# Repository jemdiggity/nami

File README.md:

# Nami 波

An internal prototype for bolt-on equipment telemetry. A split-core current clamp senses the changing magnetic field around one insulated supply conductor without an electrical connection to it. The coin-cell-powered electronics sit in an enclosure outside the equipment. The intended application is 120/240 V AC, single-phase equipment up to 20 A; suitability for that installation remains to be validated.

Nami records one RMS current value each second, retains local history, and sends measurements over Thread to a powered local hub. BLE provides commissioning. The name means “wave”: we are picking up the waves from the wire and measuring them.

- [Product requirements and system diagrams](docs/PRD.md) — authoritative prototype specification.
- [Compact C0 hardware](hardware/nami-compact/README.md) — 24 × 32 mm, four-layer production layout candidate, renders and STEP model.
- [Rev A bench hardware](hardware/nami-rev-a/README.md) — KiCad schematics, routed PCB, BOM, verification and bring-up guide.
- [Earlier design explorations](docs/research/) — rationale and candidate circuits; superseded where they conflict with the PRD.

Status: bench and compact hardware design; feasibility validation remains. Native KiCad schematics and a routed prototype PCB are included; firmware and physical validation are not yet complete. Accuracy, battery life, packaging, and installation suitability remain unverified. The board is not a manufacturing or mains-installation release.

## Compact PCB

The compact C0 board is 24 × 32 mm with four copper layers. These snapshots show the current KiCad layout; the clamp, battery, and enclosure are external to the board.

### 3D model

**[Open the full-color interactive 3D model](https://jemdiggity.github.io/nami/viewer/)** — rotate, pan, zoom, or switch between front and back views. Click the preview below to open it.

[Download GLB with materials](docs/viewer/nami.glb) · [Download STEP for CAD](hardware/nami-compact/exports/nami-compact.step) · [Download STL](https://github.com/jemdiggity/nami/raw/refs/heads/main/hardware/nami-compact/exports/nami-compact.stl)

The interactive viewer uses GLB (glTF), preserving separate meshes and component colors with material finishes adjusted for browser lighting. STEP remains available for CAD, and STL for geometry-only viewing. Models use the available KiCad component bodies and are not a validated mechanical assembly.

### Front and back

| Front | Back |
| --- | --- |
|  |  |

[STEP model](hardware/nami-compact/exports/nami-compact.step) · [PCB layout](hardware/nami-compact/nami.kicad_pcb) · [Routing review](hardware/nami-compact/exports/routing-review.pdf)

## Schematics

The previews below are vector SVG exports from the compact KiCad project. Open an image to zoom in. The [complete schematic PDF](hardware/nami-compact/exports/nami-schematic.pdf) and [native KiCad schematic](hardware/nami-compact/nami.kicad_sch) are also available.

### Analog sensing

<details>
<summary>System overview</summary>

</details>

<details>
<summary>Power supply</summary>

</details>

<details>
<summary>Radio, processor, and storage</summary>

</details>

<details>
<summary>Clamp and wiring harness</summary>

</details>

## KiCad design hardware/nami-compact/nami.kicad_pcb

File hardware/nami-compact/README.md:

# Nami Compact C0 — production layout candidate

**24 × 32 mm, four copper layers, 1.0 mm nominal PCB thickness, components on both sides.** This reduces board area from the Rev A bench board's 7,125 mm² to 768 mm²: **89.22% smaller**. Open [nami.kicad_pro](nami.kicad_pro) in KiCad 10.

This is a routed, checked candidate for the product's electronics, not a qualified production release. The dimensions describe the PCB alone. Battery/holder, CT, burden assembly, wiring, strain relief and enclosure are separate. Accuracy, endurance and installed RF performance remain unmeasured.

| Review artifact | Contents |
|---|---|
| [Front render](exports/nami-top.png) / [back render](exports/nami-bottom.png) | Actual KiCad board geometry and library component models |
| [Size comparison](exports/size-comparison.svg) | Board outlines to scale |
| [Schematic PDF](exports/nami-schematic.pdf) | Five sheets, including the off-board CT burden |
| [STEP model](exports/nami-compact.step) | Board and available library models for initial enclosure work; not a certified component tolerance model |
| [BOM](exports/bom.csv) | Package changes and preliminary parts; PCB contacts/test pads are not purchased components |
| [Routing review: before / after](exports/routing-review.pdf) | Ten close-ups covering the flagged routing details; ground fills hidden for clarity |
| [Layout verification](verification/compact-layout.json) | Dimensions, circuit equivalence, layer use and critical route lengths |
| [ERC](verification/erc.rpt) / [DRC](verification/drc.rpt) | Electrical, clearance, connectivity and schematic parity checks |

## What changed

The circuit and pin assignments are electrically equivalent to [Rev A](../nami-rev-a/README.md). It still uses the SCT006 20 A : 25 mA clamp, a permanent 5 Ω burden at the head, two ADC ranges, Thread/BLE, 16 MiB flash, and a 3 V regulated supply. No sensing range or battery-life claim has been changed to achieve the smaller outline.

- Most resistors and small capacitors use 0603 packages. The bulk capacitors, larger capacitance values and 22/47 nF C0G filters retain larger packages. Their effective capacitance and exact sourcing still need confirmation.
- U2 is **OPA2333AIDGKR in VSSOP-8**, with the same pinout and amplifier function as the bench SOIC part. [TI package information](https://www.ti.com/lit/gpn/OPA2333).
- SW1 and SW2 use **B3U-1000P** surface-mount buttons. [Manufacturer information](https://components.omron.com/us-en/products/switches/B3U).
- CT and battery headers become two solder pads each. Programming uses a custom ten-pad pogo fixture with the original ARM SWD pin numbering; analog debug uses four pogo pads. These are not sockets or a standard Tag-Connect footprint.
- The radio and analog/power circuits are on the front. Flash, bulk input storage, service contacts and buttons occupy the back. The PCB needs an enclosure cradle and local support under the buttons; there are no mounting holes.
- The same module and flash remain to limit electrical changes. A bare radio SoC or smaller flash package could reduce area further, at the cost of new RF/package engineering and additional validation. C0 is a practical compact layout, not a proven global minimum.

## Copper and assembly plan

| Layer | Role |
|---|---|
| L1 / F.Cu | Radio, analog and power components; short critical routes; ground fill |
| L2 / In1.Cu | Ground reference plane; **no routed signal tracks** |
| L3 / In2.Cu | Limited signal routing |
| L4 / B.Cu | Flash, service and battery-side components; signal routing; ground fill |

The nominal 1.0 mm construction is a mechanical target. Laminate, copper weights and dielectric thicknesses must be agreed with the fabricator before release; no controlled-impedance external RF feed is routed on this carrier. The module contains its antenna/feed. Use a conventional four-layer process, 0.15 mm minimum clearance/track constraint, 0.18 mm default signal tracks, and 0.50/0.25 mm through vias. No blind or buried vias are used. Inspect and agree solder-mask registration/tenting with the fabricator. Assembly requires two-sided reflow and a custom programming/test fixture.

The TPS63900 input/output and switch-node connections were placed and routed explicitly before the remaining local autorouting. LX1 and LX2 each have about 3.62 mm total routed length and **zero vias**. Ground pours are stitched to L2; the input/output capacitor returns and exposed pad have local ground connections. This follows TI's emphasis on short power loops, but does not replace oscilloscope/EMI testing. [TPS63900 layout guidance](https://www.ti.com/lit/ds/symlink/tps63900.pdf).

RF placement uses the north board edge and a **24 × 4 mm copper exclusion on all four layers**, plus the module footprint's local restrictions. The module maker requires no ground beneath the antenna on any layer and recommends placing it at the PCB edge. [Raytac layout guidance, section 2.3](https://www.raytac.com/tw/download/index.php?index_id=24). Metal from a battery, mounting hardware or an outlet box must not occupy the antenna's surrounding volume. The carrier ground area is much smaller than the bench board; range and antenna tuning need measurement in the intended enclosure.

## Connections and packaging

The [Rev A pin table and bring-up sequence](../nami-rev-a/README.md#connectors-and-firmware-assignment) remain applicable, except that J1–J4 now use bare contact pads and U2 has a different package.

| Interface | Compact implementation |
|---|---|
| J1, front southwest | 1 = CT signal, 2 = VMID. Permanent 5 Ω burden stays at the clamp, before the detachable harness. VMID is not GND. |
| J2, back southeast in front-view coordinates | 1 = battery positive, 2 = GND. Single 2.0–3.3 V source; no charger or reverse-polarity protection. |
| J3, back | Ten pads on 1.27 mm pitch, ARM SWD numbering. VTref senses the target rail; do not power through the debug fixture. |
| J4, back | 1 low ADC, 2 high ADC, 3 VMID, 4 GND, 1.27 mm pitch. |
| SW1 / SW2, back | Pair / reset; enclosure must provide access and mechanical support. |

Use the native footprint pad numbers to build the jig. The bottom render is viewed from below and therefore mirrors the front coordinate system. Wire pads require external strain relief and insulated joints; they cannot support the clamp or battery mechanically. Keep fixture contacts accessible before final enclosure assembly. A board-specific fixture can locate against the PCB edges; its tooling is not designed here.

The **CR2450 remains an external candidate**, approximately 24.5 mm diameter by 5 mm thick before its holder. It is already slightly wider than the PCB, and cannot simply be stacked behind the antenna. No integrated 24 × 32 mm device envelope is claimed. The SCT006 is also a separate, roughly 29 × 16.5 × 19 mm clamp. Prefer faceplate-side electronics and a remote clamp in the box; the final antenna location, battery service access and conductor/insulation clearances require enclosure design. [Battery dimensions](https://energy.panasonic.com/dam/master/pdf/en/datasheet/lithium/CR2450_Datasheet_EN.pdf), [CT dimensions](https://www.poweruc.pl/products/split-core-current-transformer-sct006-rated-input-20a).

## Verification and remaining release work

Recorded checks pass with zero ERC violations, zero DRC violations, zero unconnected items and zero schematic/PCB mismatches. Independent checks verify all 59 electrical footprint entries against the schematic manifest, 51 critical pin connections, and identical electrical nets to Rev A. Compact-specific checks verify the outline, substrate target, all-layer antenna exclusion, ground-plane layer and via-free switching paths. These checks establish CAD consistency, not measured product performance.

Before ordering a production run:

1. Audit exact ordered parts against footprints, capacitor derating and assembly tolerances. Finalize the fabricator stackup, panel/rail strategy and fixture. Validate small contact pads and button access against the enclosure.
2. Validate low-current noise, clipping recovery and ±10% RMS performance with the radio and flash active. Repeat the isolated low-voltage bring-up from Rev A.
3. Close the energy budget. Continuous ADC acquisition, the amplifier's roughly 34 µA typical total quiescent current and flash activity still make the one-year coin-cell target uncertain. Verify startup and flash/radio bursts against the regulator's 25 mA input limit and actual battery impedance.
4. Measure RF range in the proposed faceplate/box installation, with the battery and mounting hardware in place. Confirm mechanical insulation, thermal behavior and applicable installation/product requirements before field use.

Firmware, hub software, calibration, enclosure, battery endurance and qualification remain outstanding. No manufacturing release or claim of mains-installation suitability accompanies this layout.

## Reproduce

The committed native CAD is the review result. The scripts overwrite generated files: preserve manual edits before using them. Run commands from the repository root. Use ordinary Python with `sexpdata` for generation and KiCad's bundled Python for `pcbnew` scripts.

1. `NAMI_VARIANT=compact python hardware/tools/generate.py`
2. Run `hardware/tools/compact_board.py` with KiCad Python. This creates local contact footprints, a fresh board, hand-routed power paths and `nami.dsn`.
3. Reuse the matching committed `nami.ses`, or run Freerouting 2.0.1 locally against that DSN. L2 is marked as a power layer in the routing exchange. Changed placement or critical routes require a new session.
4. Run `hardware/tools/compact_finish.py` with KiCad Python to import the session, fill ground, stitch ground regions, and apply `refine_routes.py`. The refinement moves the crystal/load capacitors and selected vias, and replaces the reviewed routing details. Do not apply it a second time to a finished board.
5. Export KiCad XML netlist to `exports/nami-netlist.xml`; run `NAMI_VARIANT=compact ... hardware/tools/sync_board.py` with KiCad Python.
6. Run KiCad ERC and PCB DRC with `--schematic-parity --exit-code-violations`; run `NAMI_VARIANT=compact python hardware/tools/verify.py` and `hardware/tools/compact_verify.py` with KiCad Python. Regenerate review PDF, renders and STEP after changes.

Local connector footprints live in `Nami.pretty` and `fp-lib-table`. Other symbols/footprints use the installed KiCad libraries. `NAMI_VARIANT` defaults to the original bench design; selecting compact does not overwrite it.

### Layout review, 2026-09-26

The analog sheet now draws the midpoint voltage follower, input network, non-inverting gain stage, feedback resistors and ADC filters with direct wires. Decoupling remains separate. This presentation is shared with the bench design and preserves the original electrical nets.

The reviewed routing changes align C13/C14 with Y1, remove the module supply loop/spur, straighten the CT return pad exits, replace pair/MOSI jogs, improve rear supply and flash pad exits, and move the battery split into C1 instead of an external right-angle T. The clock via and two ground stitching vias move to maintain clearance. The 24 × 32 mm outline, power-loop routes, four-layer construction and component values remain unchanged. See the before/after PDF above.

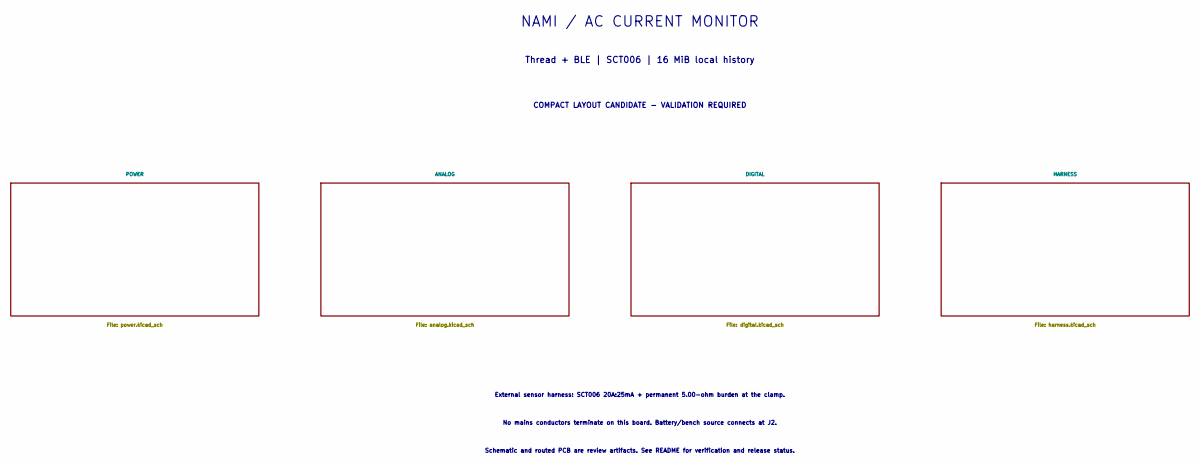
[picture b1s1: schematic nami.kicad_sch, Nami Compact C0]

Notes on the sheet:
NAMI / AC CURRENT MONITOR
Thread + BLE | SCT006 | 16 MiB local history
COMPACT LAYOUT CANDIDATE - VALIDATION REQUIRED
External sensor harness: SCT006 20A:25mA + permanent 5.00-ohm burden at the clamp.
No mains conductors terminate on this board. Battery/bench source connects at J2.
Schematic and routed PCB are review artifacts. See README for verification and release status.

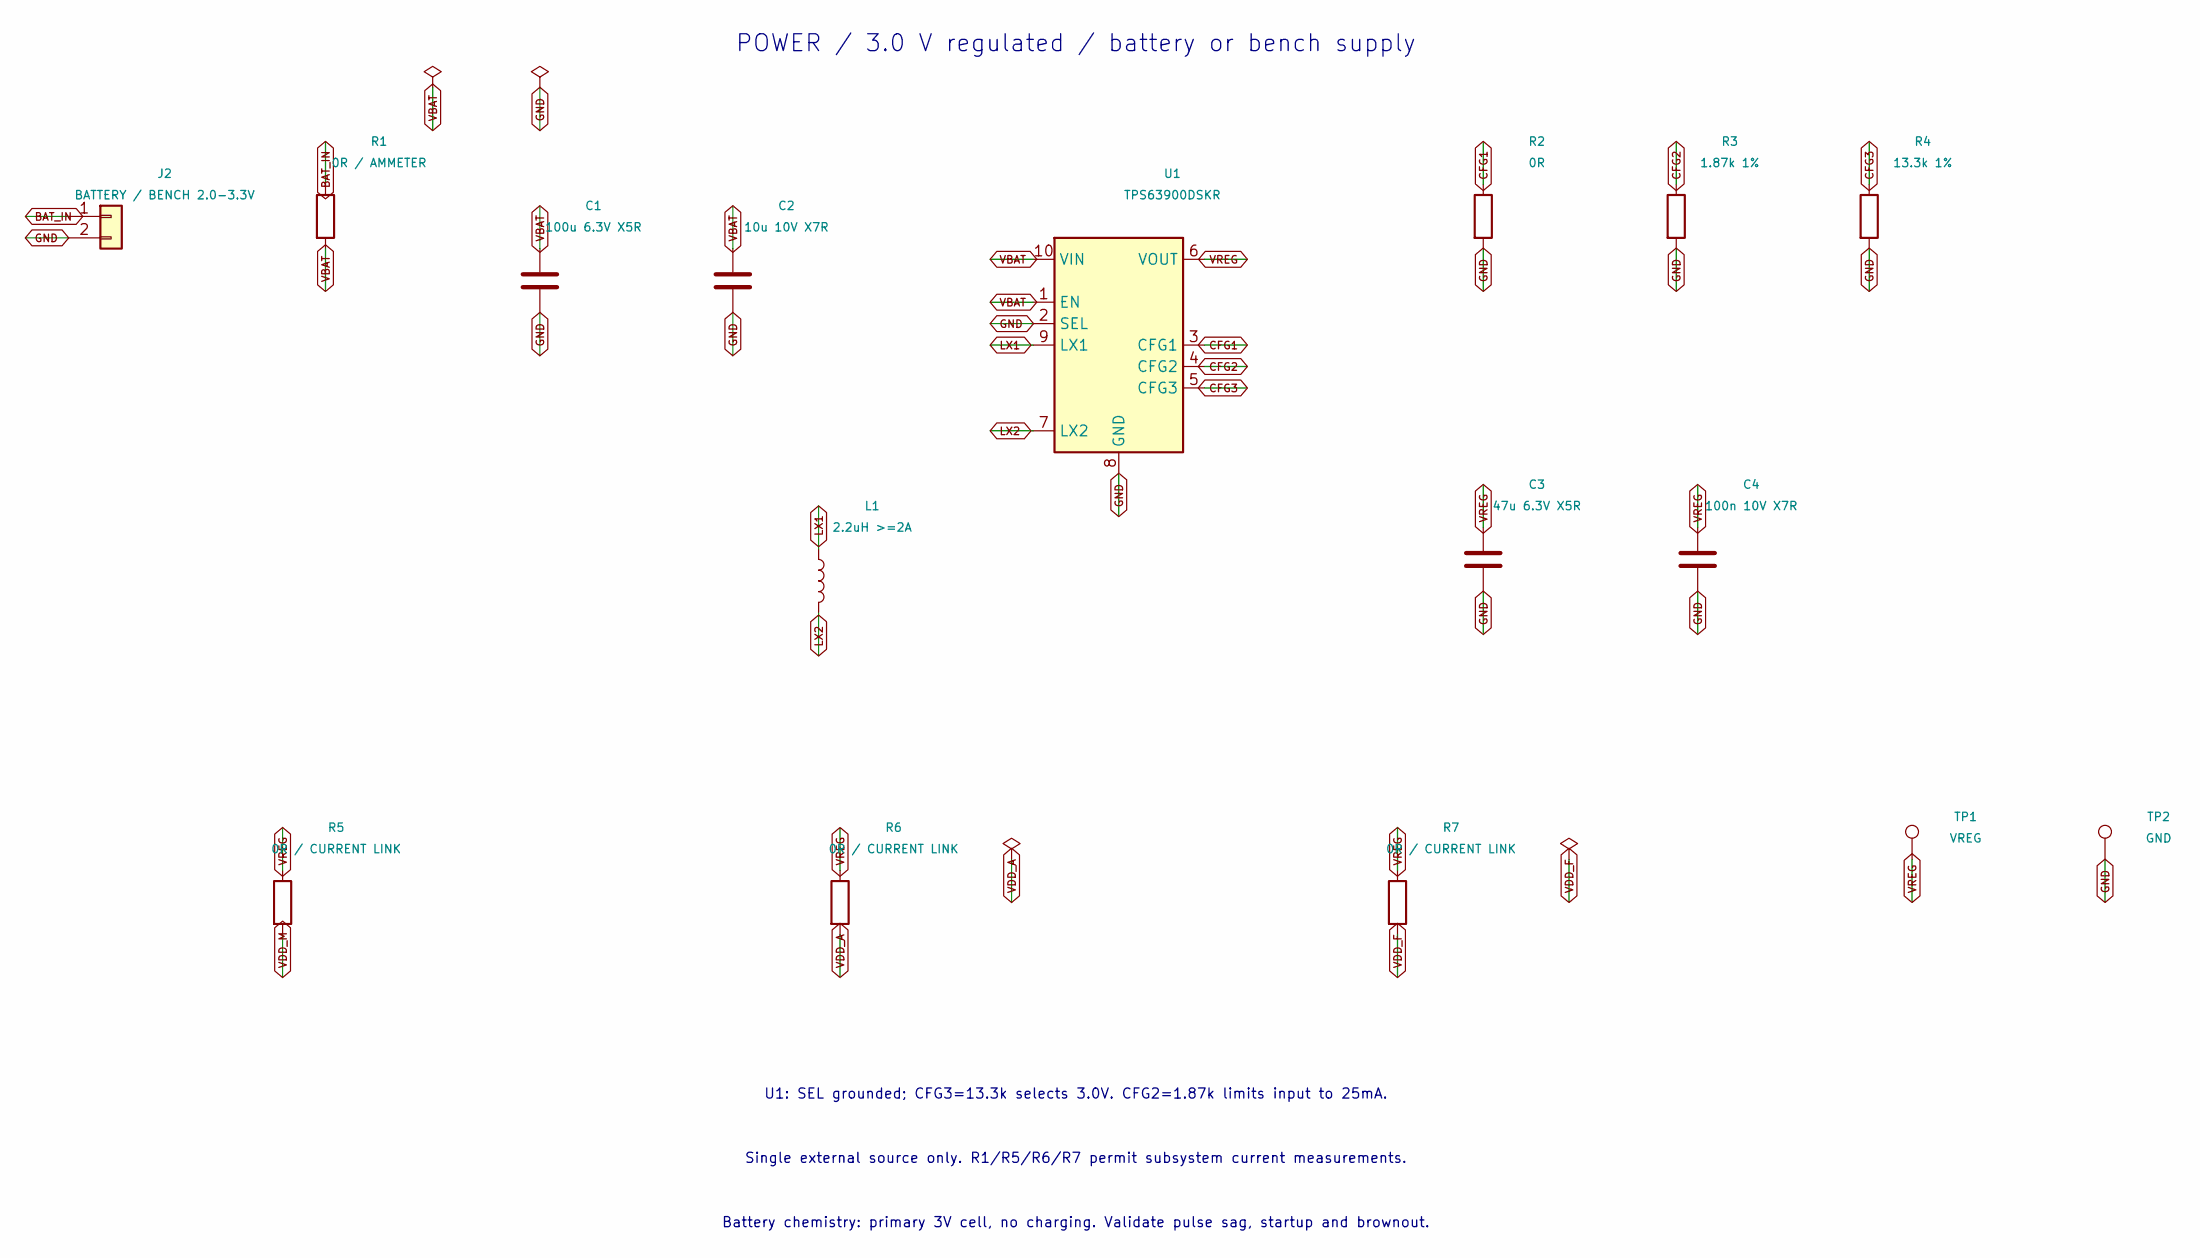
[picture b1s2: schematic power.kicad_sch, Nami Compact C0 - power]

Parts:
C1: 100u 6.3V X5R; C_1210_3225Metric; MPN GRM32ER60J107ME20L
C2: 10u 10V X7R; C_0805_2012Metric
C3: 47u 6.3V X5R; C_1210_3225Metric
C4: 100n 10V X7R; C_0603_1608Metric
J2: BATTERY / BENCH 2.0-3.3V; WirePads_2_P2.5
L1: 2.2uH >=2A; L_Coilcraft_XAL4020-XXX; MPN XAL4020-222MEC
R1: 0R / AMMETER; R_0603_1608Metric
R2: 0R; R_0603_1608Metric
R3: 1.87k 1%; R_0603_1608Metric
R4: 13.3k 1%; R_0603_1608Metric
R5, R6, R7: 0R / CURRENT LINK; R_0603_1608Metric
TP1: VREG; TestPoint_Pad_D1.0mm
TP2: GND; TestPoint_Pad_D1.0mm
U1: TPS63900DSKR; WSON-10-1EP_2.5x2.5mm_P0.5mm_EP1.2x2mm; MPN TPS63900DSKR

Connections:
BAT_IN: J2.1, R1.1
CFG1: R2.1, U1.3 (CFG1)
CFG2: R3.1, U1.4 (CFG2)
CFG3: R4.1, U1.5 (CFG3)
GND: C1.2, C2.2, C3.2, C4.2, J2.2, R2.2, R3.2, R4.2, TP2.1, U1.2 (SEL), U1.8 (GND), U1.11 (GND); also elsewhere on the board
LX1: L1.1, U1.9 (LX1)
LX2: L1.2, U1.7 (LX2)
VBAT: C1.1, C2.1, R1.2, U1.1 (EN), U1.10 (VIN); also elsewhere on the board
VDD_A: R6.2; also elsewhere on the board
VDD_F: R7.2; also elsewhere on the board
VDD_M: R5.2; also elsewhere on the board
VREG: C3.1, C4.1, R5.1, R6.1, R7.1, TP1.1, U1.6 (VOUT)

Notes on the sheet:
POWER / 3.0 V regulated / battery or bench supply
U1: SEL grounded; CFG3=13.3k selects 3.0V. CFG2=1.87k limits input to 25mA.
Single external source only. R1/R5/R6/R7 permit subsystem current measurements.
Battery chemistry: primary 3V cell, no charging. Validate pulse sag, startup and brownout.

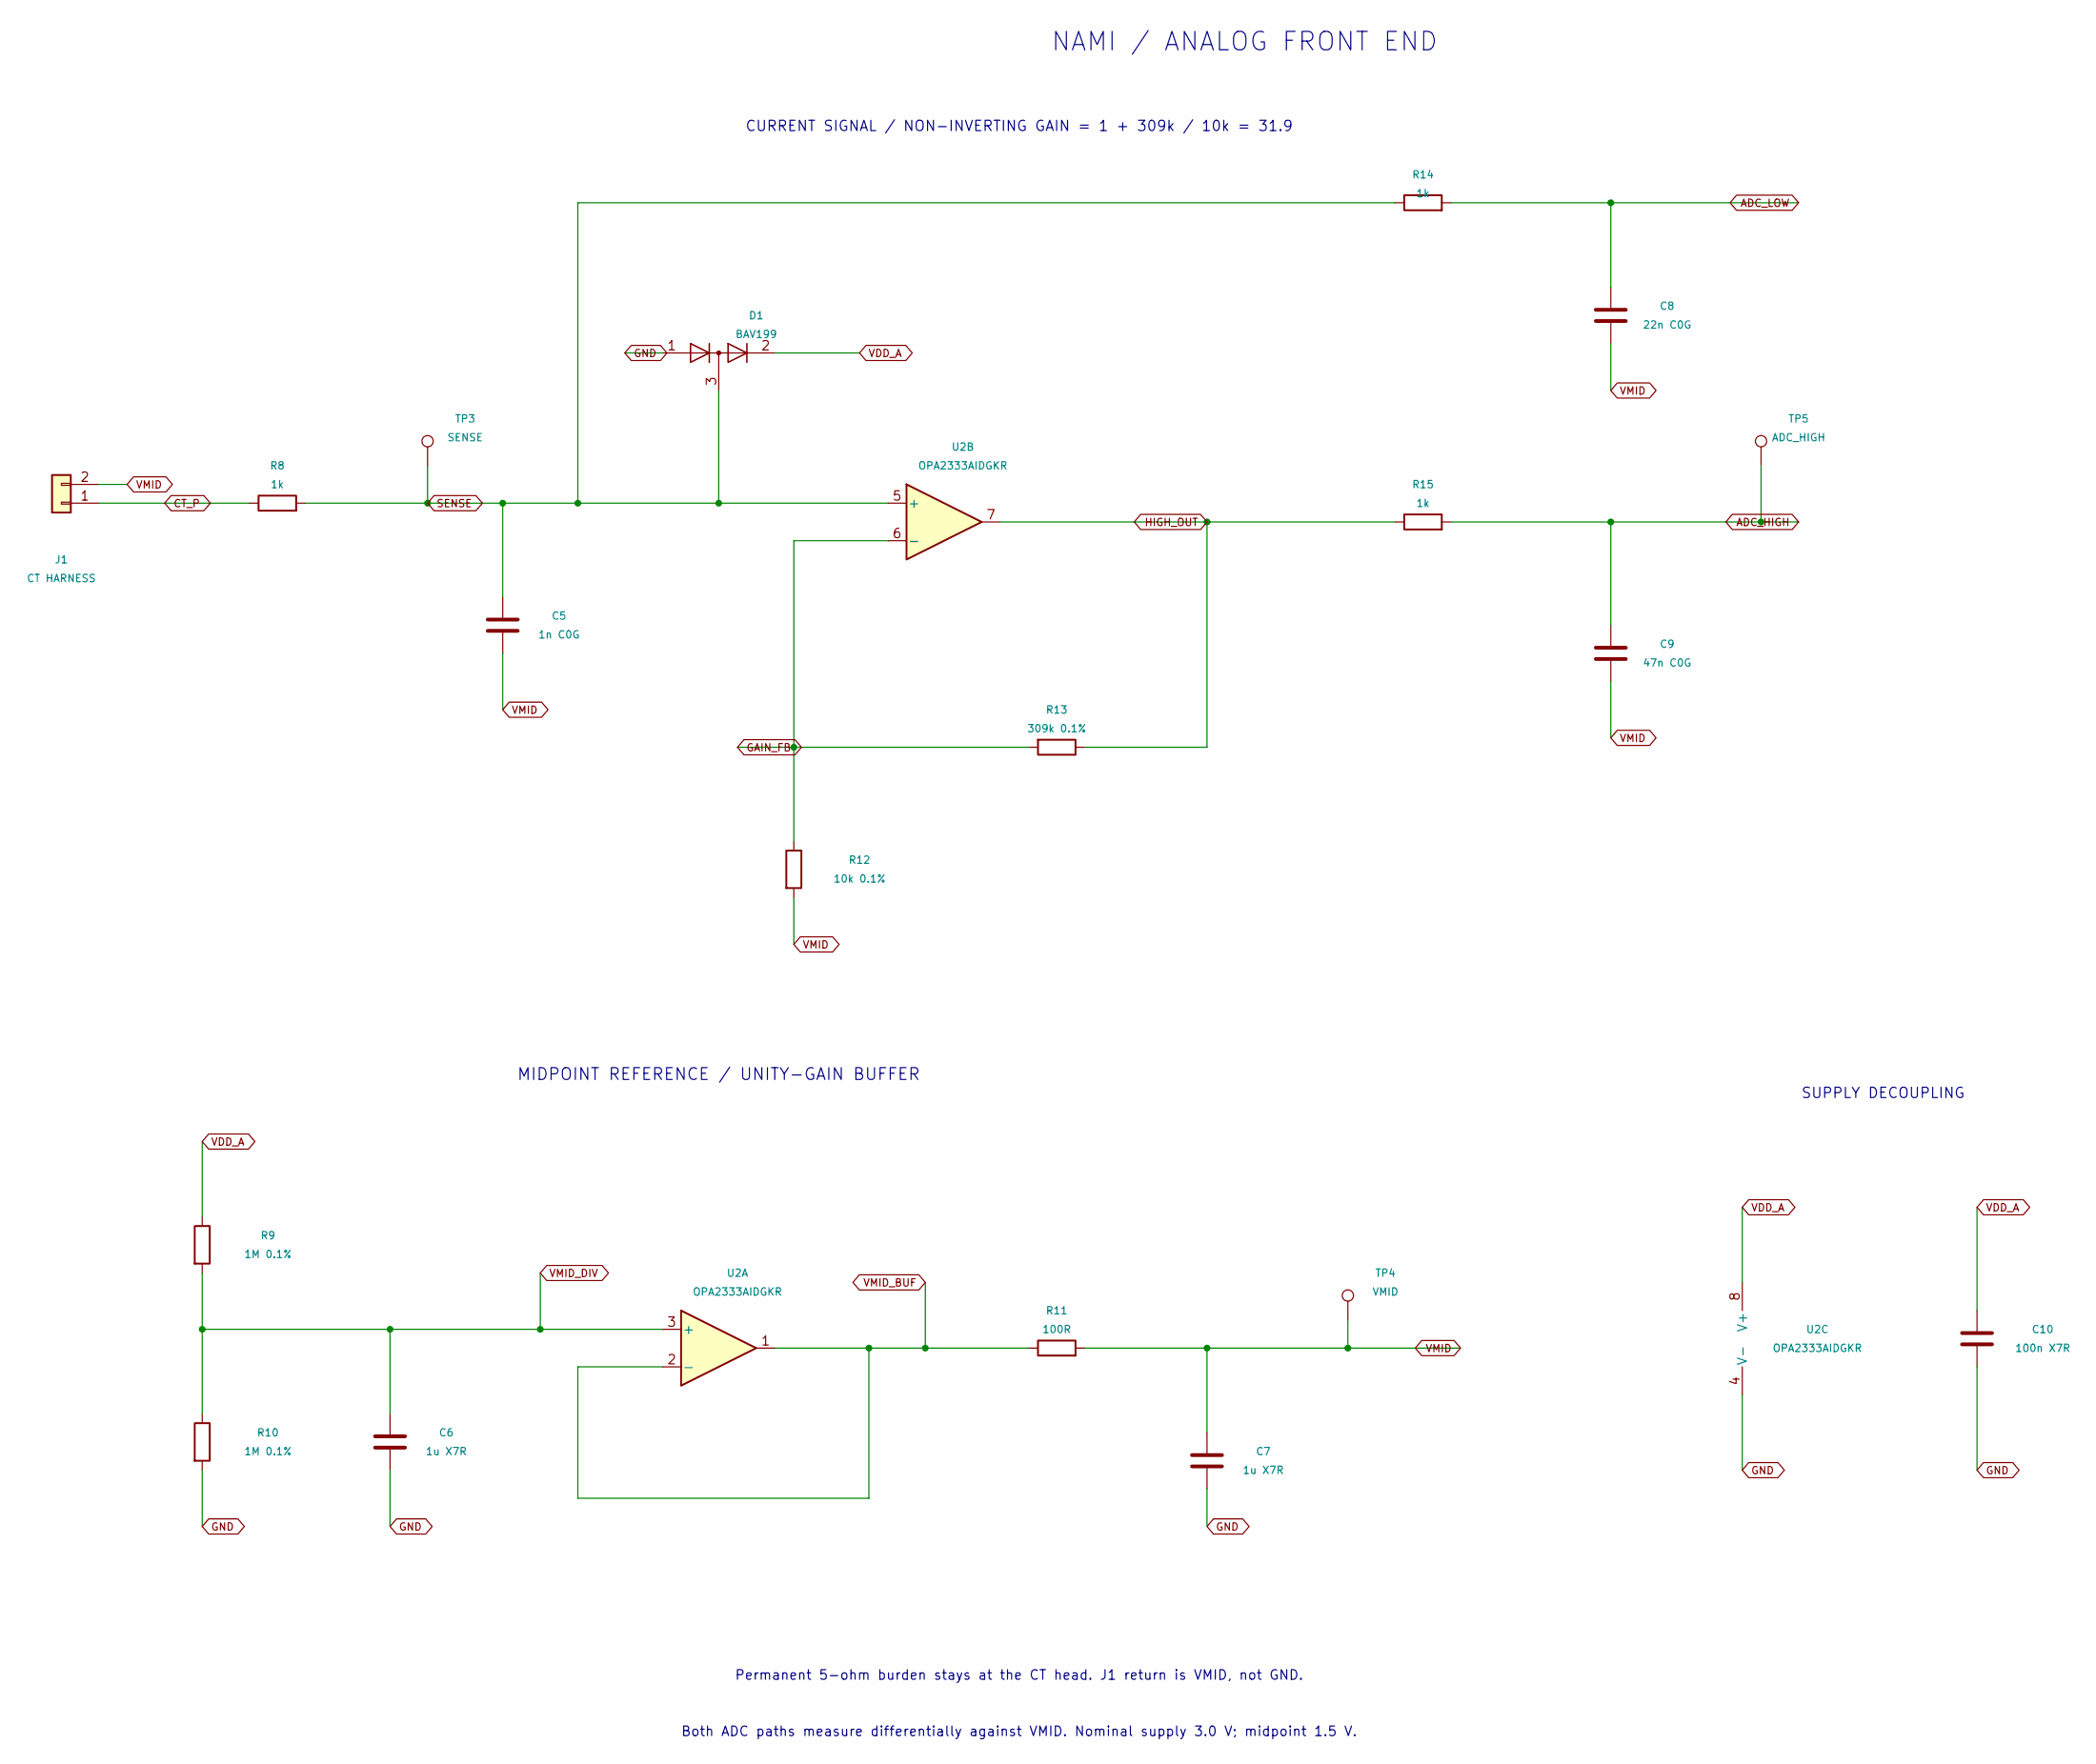
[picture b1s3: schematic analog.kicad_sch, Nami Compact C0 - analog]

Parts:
C5: 1n C0G; C_0603_1608Metric
C6, C7: 1u X7R; C_0603_1608Metric
C8: 22n C0G; C_0805_2012Metric
C9: 47n C0G; C_0805_2012Metric
C10: 100n X7R; C_0603_1608Metric
D1: BAV199; SOT-23; MPN BAV199,215
J1: CT HARNESS; WirePads_2_P2.5
R8, R14, R15: 1k; R_0603_1608Metric
R9, R10: 1M 0.1%; R_0603_1608Metric
R11: 100R; R_0603_1608Metric
R12: 10k 0.1%; R_0603_1608Metric
R13: 309k 0.1%; R_0603_1608Metric
TP3: SENSE; TestPoint_Pad_D1.0mm
TP4: VMID; TestPoint_Pad_D1.0mm
TP5: ADC_HIGH; TestPoint_Pad_D1.0mm
U2: OPA2333AIDGKR; VSSOP-8_3x3mm_P0.65mm; MPN OPA2333AIDGKR

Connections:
ADC_HIGH: C9.1, R15.2, TP5.1; also elsewhere on the board
ADC_LOW: C8.1, R14.2; also elsewhere on the board
CT_P: J1.1, R8.1
GAIN_FB: R12.1, R13.2, U2.6 (-)
GND: C6.2, C7.2, C10.2, D1.1 (K), R10.2, U2.4 (V-); also elsewhere on the board
HIGH_OUT: R13.1, R15.1, U2.7
SENSE: C5.1, D1.3 (K), R8.2, R14.1, TP3.1, U2.5 (+)
VDD_A: C10.1, D1.2 (A), R9.1, U2.8 (V+); also elsewhere on the board
VMID: C5.2, C7.1, C8.2, C9.2, J1.2, R11.2, R12.2, TP4.1; also elsewhere on the board
VMID_BUF: R11.1, U2.1, U2.2 (-)
VMID_DIV: C6.1, R9.2, R10.1, U2.3 (+)

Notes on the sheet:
NAMI / ANALOG FRONT END
CURRENT SIGNAL / NON-INVERTING GAIN = 1 + 309k / 10k = 31.9
MIDPOINT REFERENCE / UNITY-GAIN BUFFER
SUPPLY DECOUPLING
Permanent 5-ohm burden stays at the CT head. J1 return is VMID, not GND.
Both ADC paths measure differentially against VMID. Nominal supply 3.0 V; midpoint 1.5 V.

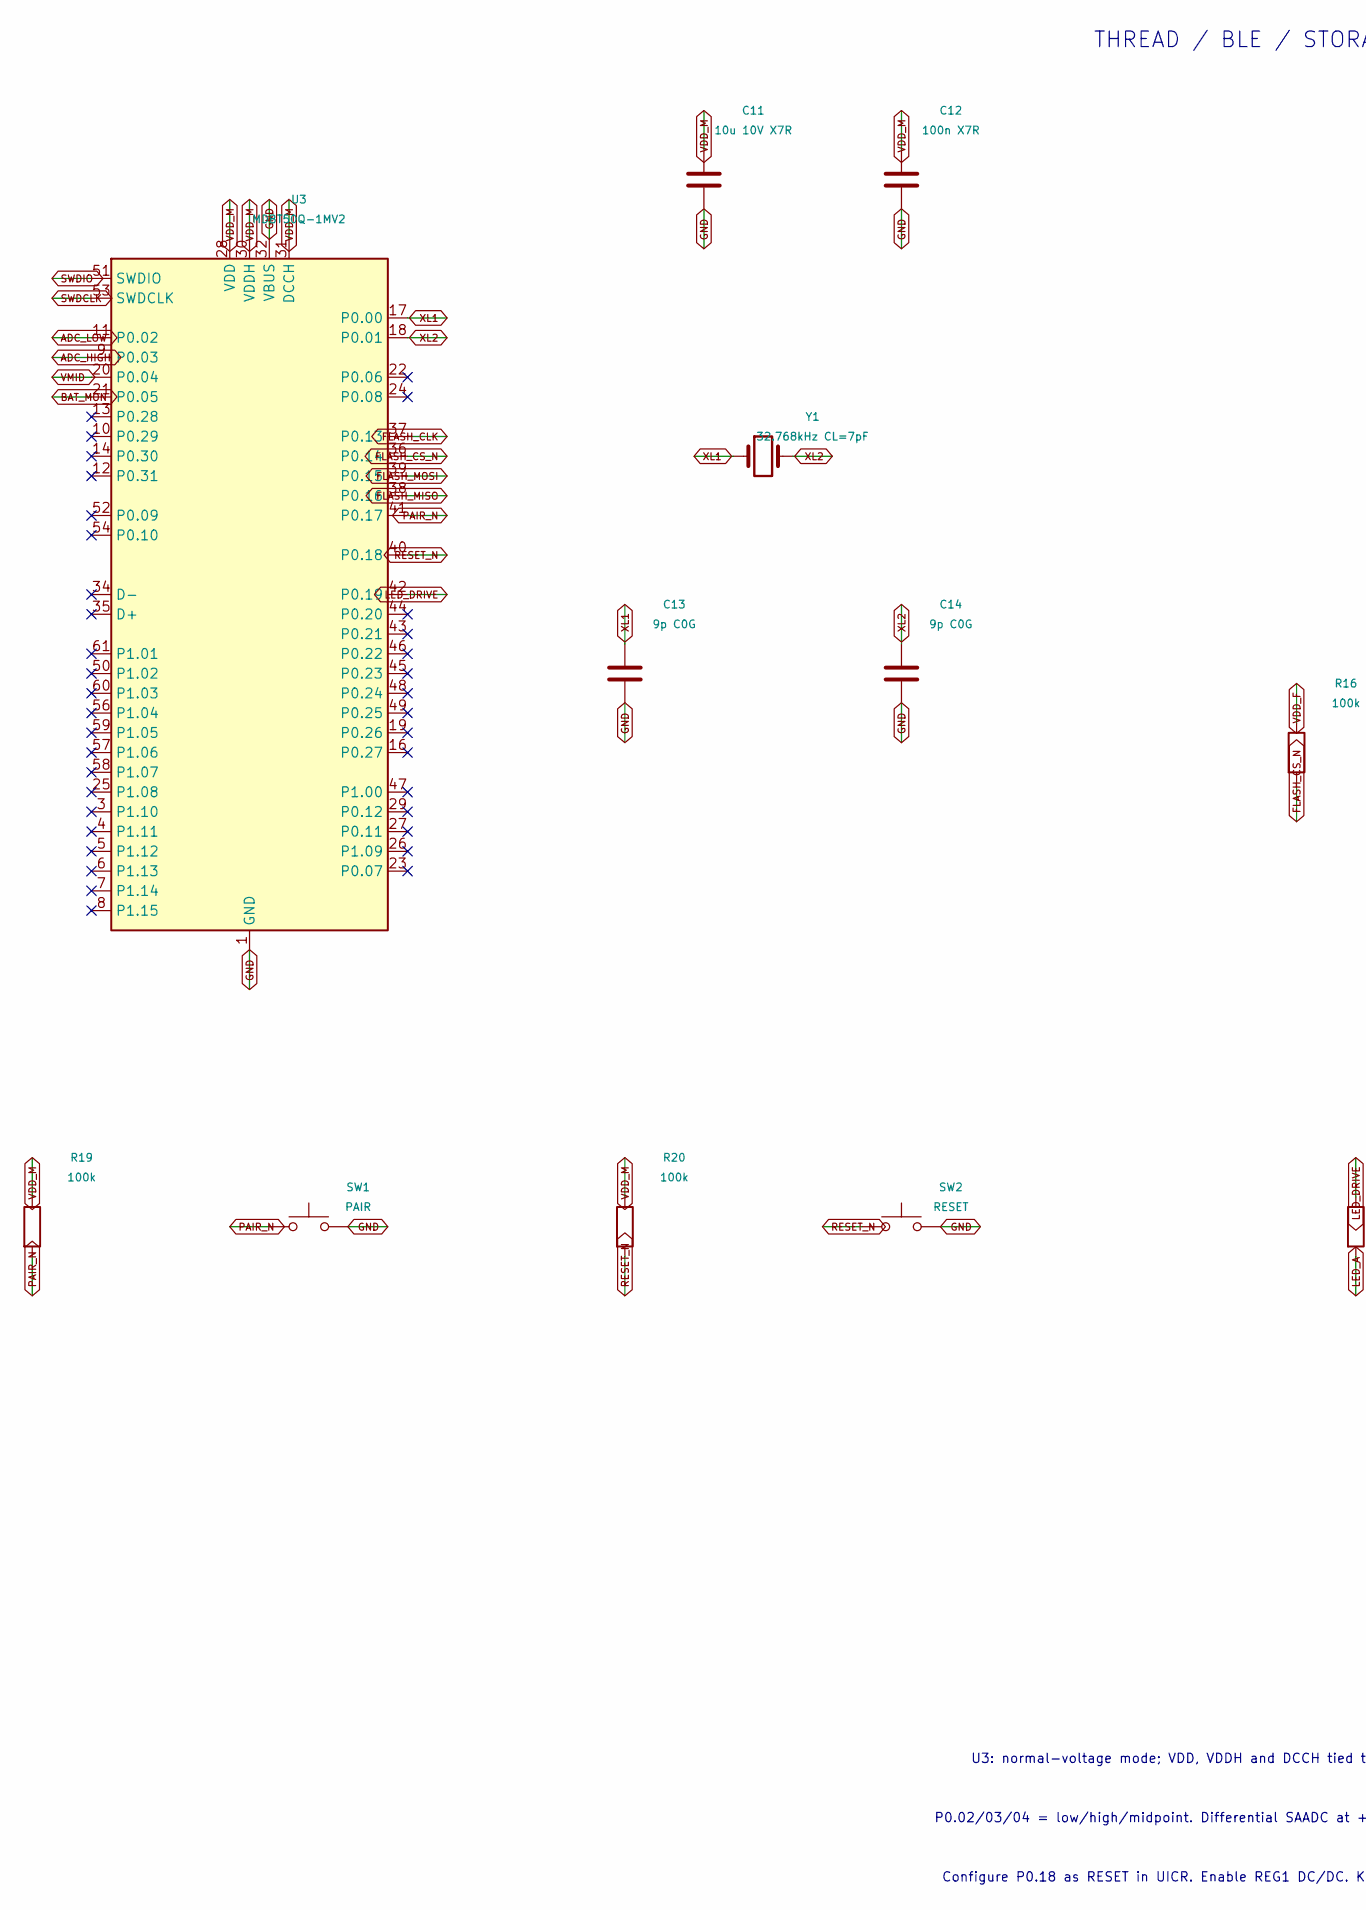
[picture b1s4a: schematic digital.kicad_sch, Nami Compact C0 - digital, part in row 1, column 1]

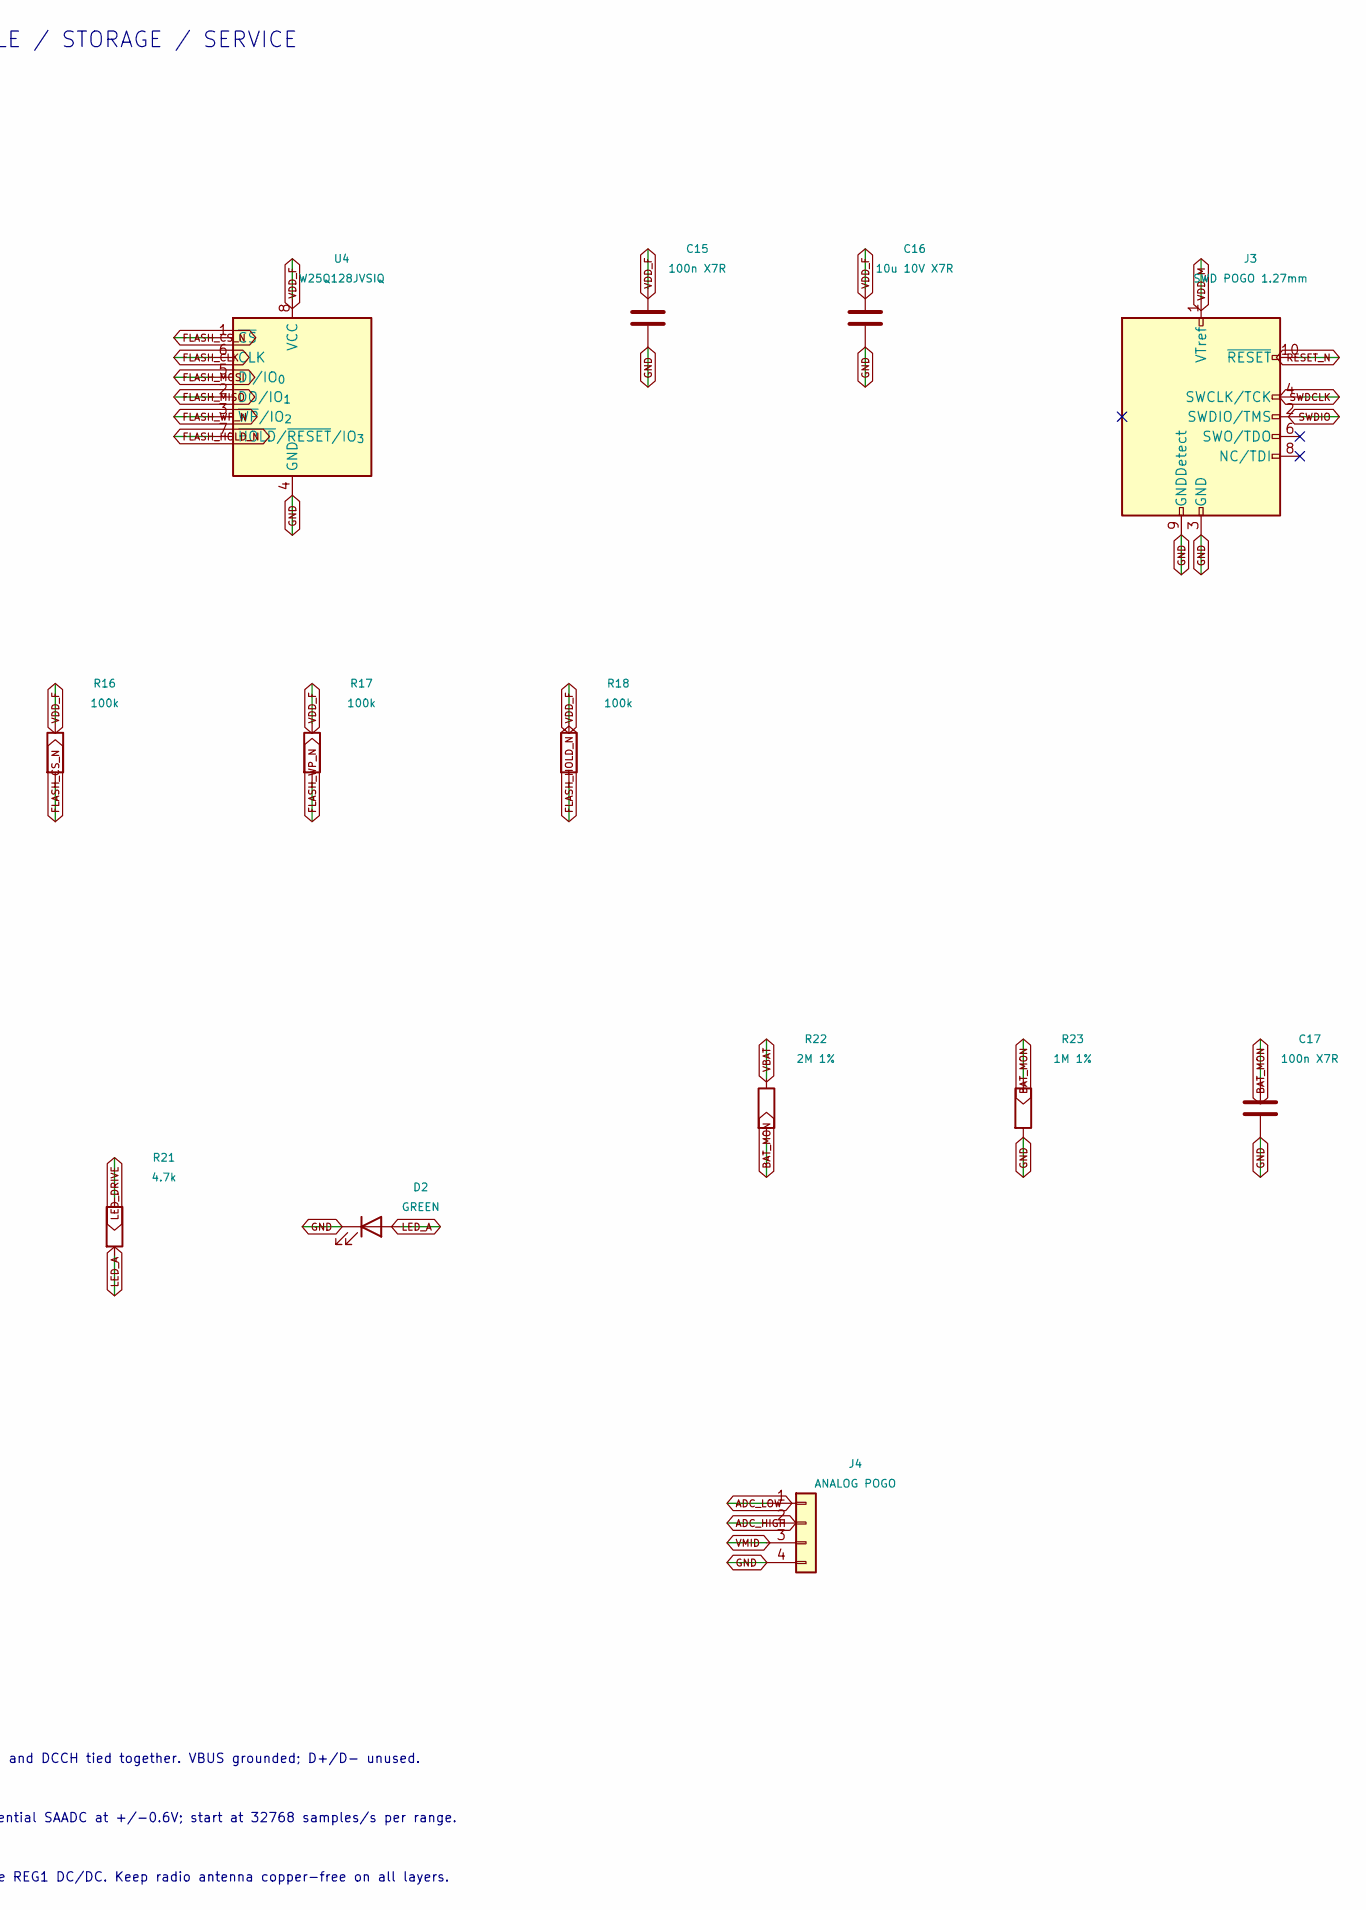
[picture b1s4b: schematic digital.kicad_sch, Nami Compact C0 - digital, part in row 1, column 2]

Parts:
C11, C16: 10u 10V X7R; C_0805_2012Metric
C12, C15, C17: 100n X7R; C_0603_1608Metric
C13, C14: 9p C0G; C_0603_1608Metric
D2: GREEN; LED_0603_1608Metric
J3: SWD POGO 1.27mm; Pogo_2x05_P1.27
J4: ANALOG POGO; Pogo_1x04_P1.27
R16, R17, R18, R19, R20: 100k; R_0603_1608Metric
R21: 4.7k; R_0603_1608Metric
R22: 2M 1%; R_0603_1608Metric
R23: 1M 1%; R_0603_1608Metric
SW1: PAIR; SW_SPST_B3U-1000P; MPN B3U-1000P
SW2: RESET; SW_SPST_B3U-1000P; MPN B3U-1000P
U3: MDBT50Q-1MV2; Raytac_MDBT50Q; MPN MDBT50Q-1MV2
U4: W25Q128JVSIQ; SOIC-8_5.3x5.3mm_P1.27mm; MPN W25Q128JVSIQ
Y1: 32.768kHz CL=7pF; Crystal_SMD_3215-2Pin_3.2x1.5mm; MPN ABS07-32.768KHZ-7-T

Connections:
ADC_HIGH: J4.2, U3.9 (P0.03); also elsewhere on the board
ADC_LOW: J4.1, U3.11 (P0.02); also elsewhere on the board
BAT_MON: C17.1, R22.2, R23.1, U3.21 (P0.05)
FLASH_CLK: U3.37 (P0.13), U4.6 (CLK)
FLASH_CS_N: R16.2, U3.36 (P0.14), U4.1 (~CS)
FLASH_HOLD_N: R18.2, U4.7 (~HOLD/~RESET/IO_{3})
FLASH_MISO: U3.38 (P0.16), U4.2 (DO/IO_{1})
FLASH_MOSI: U3.39 (P0.15), U4.5 (DI/IO_{0})
FLASH_WP_N: R17.2, U4.3 (~WP/IO_{2})
GND: C11.2, C12.2, C13.2, C14.2, C15.2, C16.2, C17.2, D2.1 (K), J3.3 (GND), J3.5 (GND), J3.9 (GNDDetect), J4.4, R23.2, SW1.2, SW2.2, U3.1 (GND), U3.2 (GND), U3.15 (GND), U3.32 (VBUS), U3.33 (GND), U3.55 (GND), U4.4 (GND); also elsewhere on the board
LED_A: D2.2 (A), R21.2
LED_DRIVE: R21.1, U3.42 (P0.19)
PAIR_N: R19.2, SW1.1, U3.41 (P0.17)
RESET_N: J3.10 (~RESET), R20.2, SW2.1, U3.40 (P0.18)
SWDCLK: J3.4 (SWCLK/TCK), U3.53 (SWDCLK)
SWDIO: J3.2 (SWDIO/TMS), U3.51 (SWDIO)
VBAT: R22.1; also elsewhere on the board
VDD_F: C15.1, C16.1, R16.1, R17.1, R18.1, U4.8 (VCC); also elsewhere on the board
VDD_M: C11.1, C12.1, J3.1 (VTref), R19.1, R20.1, U3.28 (VDD), U3.30 (VDDH), U3.31 (DCCH); also elsewhere on the board
VMID: J4.3, U3.20 (P0.04); also elsewhere on the board
XL1: C13.1, U3.17 (P0.00), Y1.1
XL2: C14.1, U3.18 (P0.01), Y1.2

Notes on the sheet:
THREAD / BLE / STORAGE / SERVICE
U3: normal-voltage mode; VDD, VDDH and DCCH tied together. VBUS grounded; D+/D- unused.
P0.02/03/04 = low/high/midpoint. Differential SAADC at +/-0.6V; start at 32768 samples/s per range.
Configure P0.18 as RESET in UICR. Enable REG1 DC/DC. Keep radio antenna copper-free on all layers.

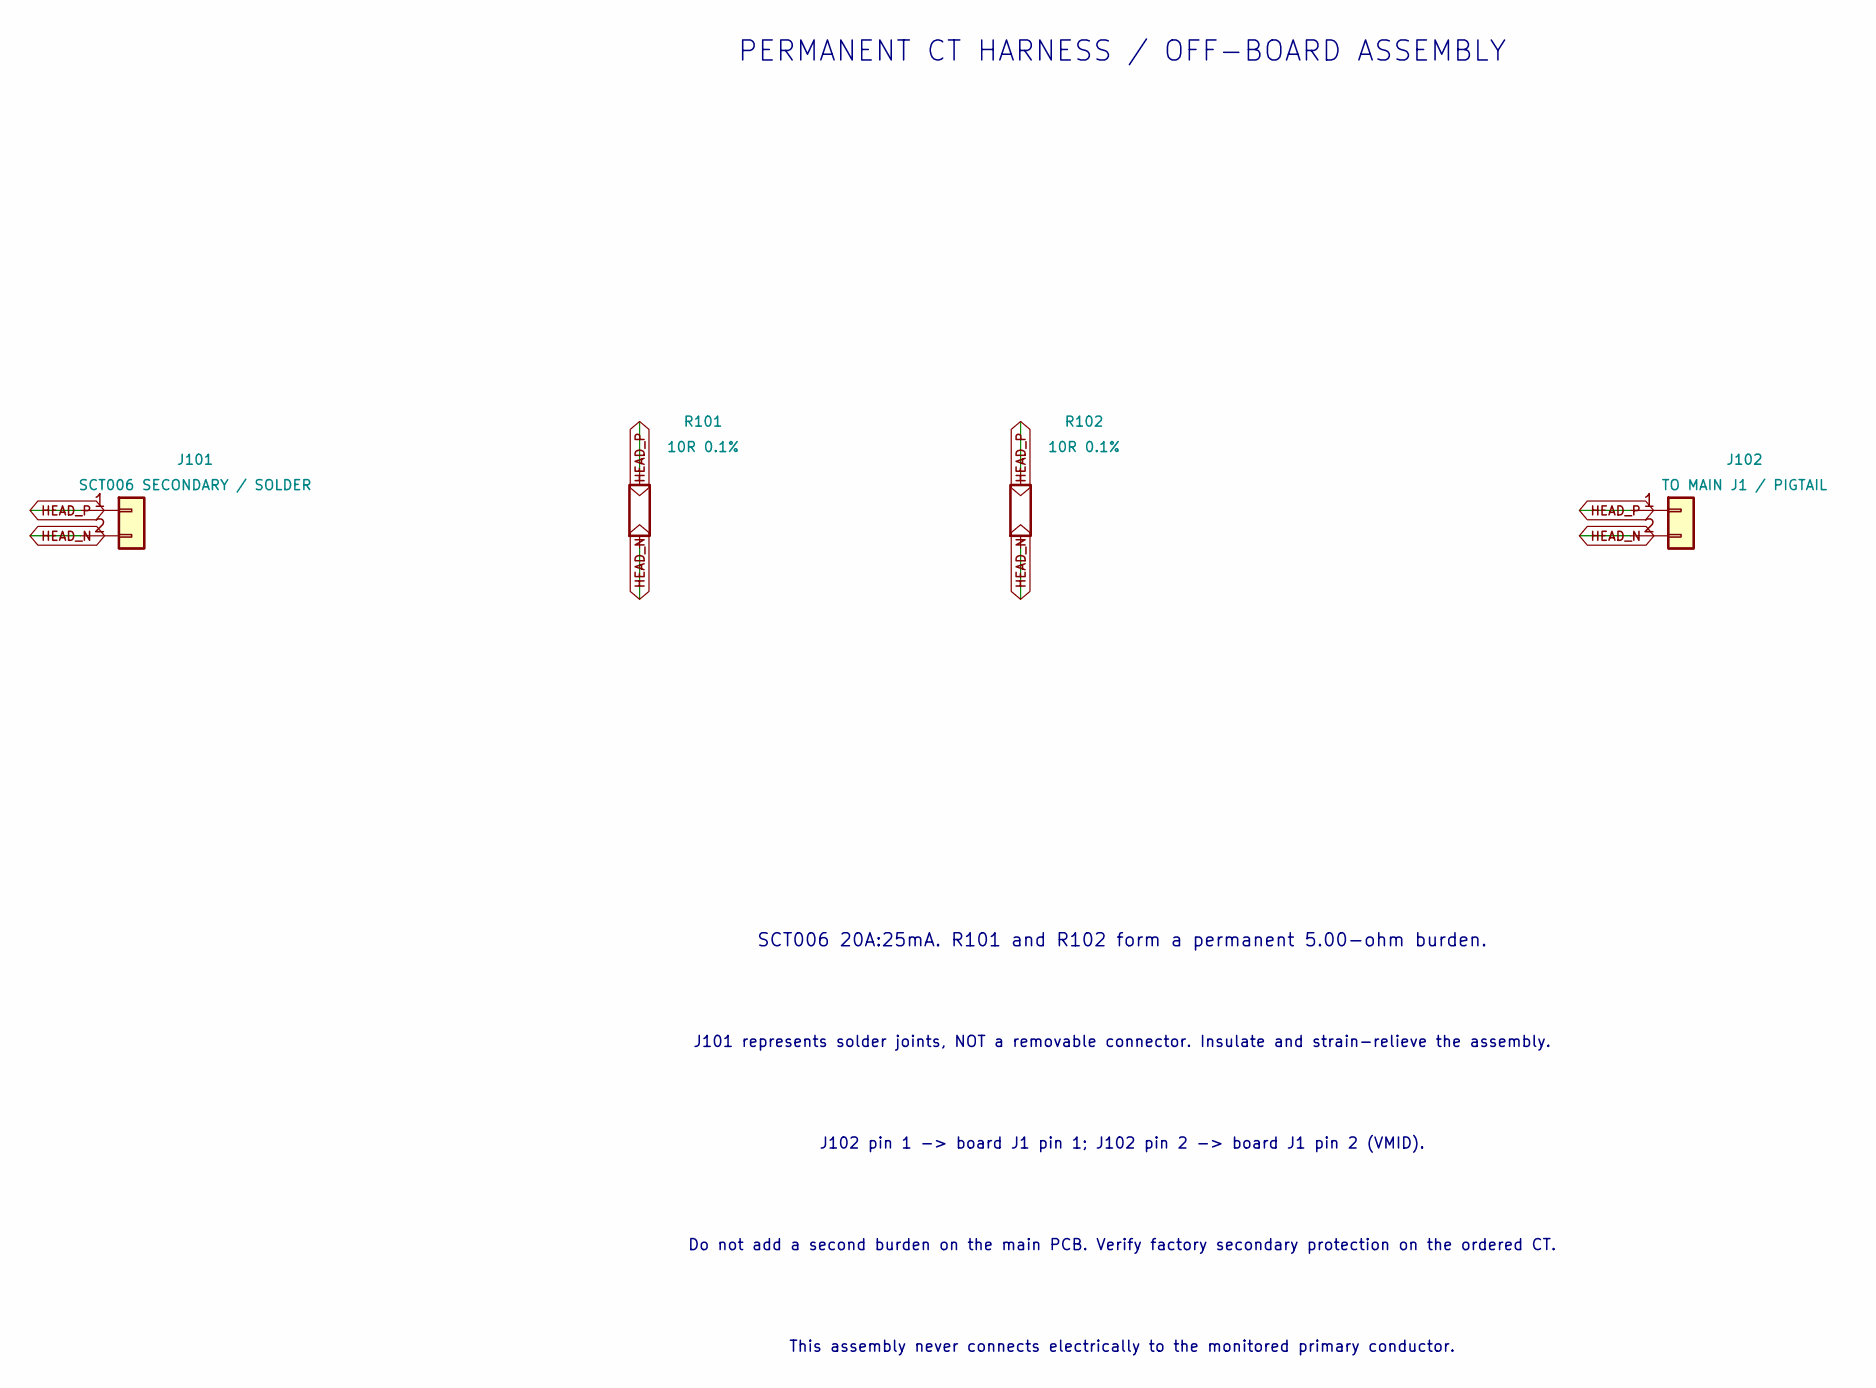
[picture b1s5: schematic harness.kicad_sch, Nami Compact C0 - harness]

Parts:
J101: SCT006 SECONDARY / SOLDER; PinHeader_1x02_P2.54mm_Vertical
J102: TO MAIN J1 / PIGTAIL; PinHeader_1x02_P2.54mm_Vertical
R101, R102: 10R 0.1%; R_0805_2012Metric

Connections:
unnamed: J101.1, J102.1, R101.1, R102.1
unnamed: J101.2, J102.2, R101.2, R102.2

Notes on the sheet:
PERMANENT CT HARNESS / OFF-BOARD ASSEMBLY
SCT006 20A:25mA. R101 and R102 form a permanent 5.00-ohm burden.
J101 represents solder joints, NOT a removable connector. Insulate and strain-relieve the assembly.
J102 pin 1 -> board J1 pin 1; J102 pin 2 -> board J1 pin 2 (VMID).
Do not add a second burden on the main PCB. Verify factory secondary protection on the ordered CT.
This assembly never connects electrically to the monitored primary conductor.
